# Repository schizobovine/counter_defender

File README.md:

counter_defender
================

PIR motion sensor alarm to keep the cats off the countertop. Modular. Also ridiculous.

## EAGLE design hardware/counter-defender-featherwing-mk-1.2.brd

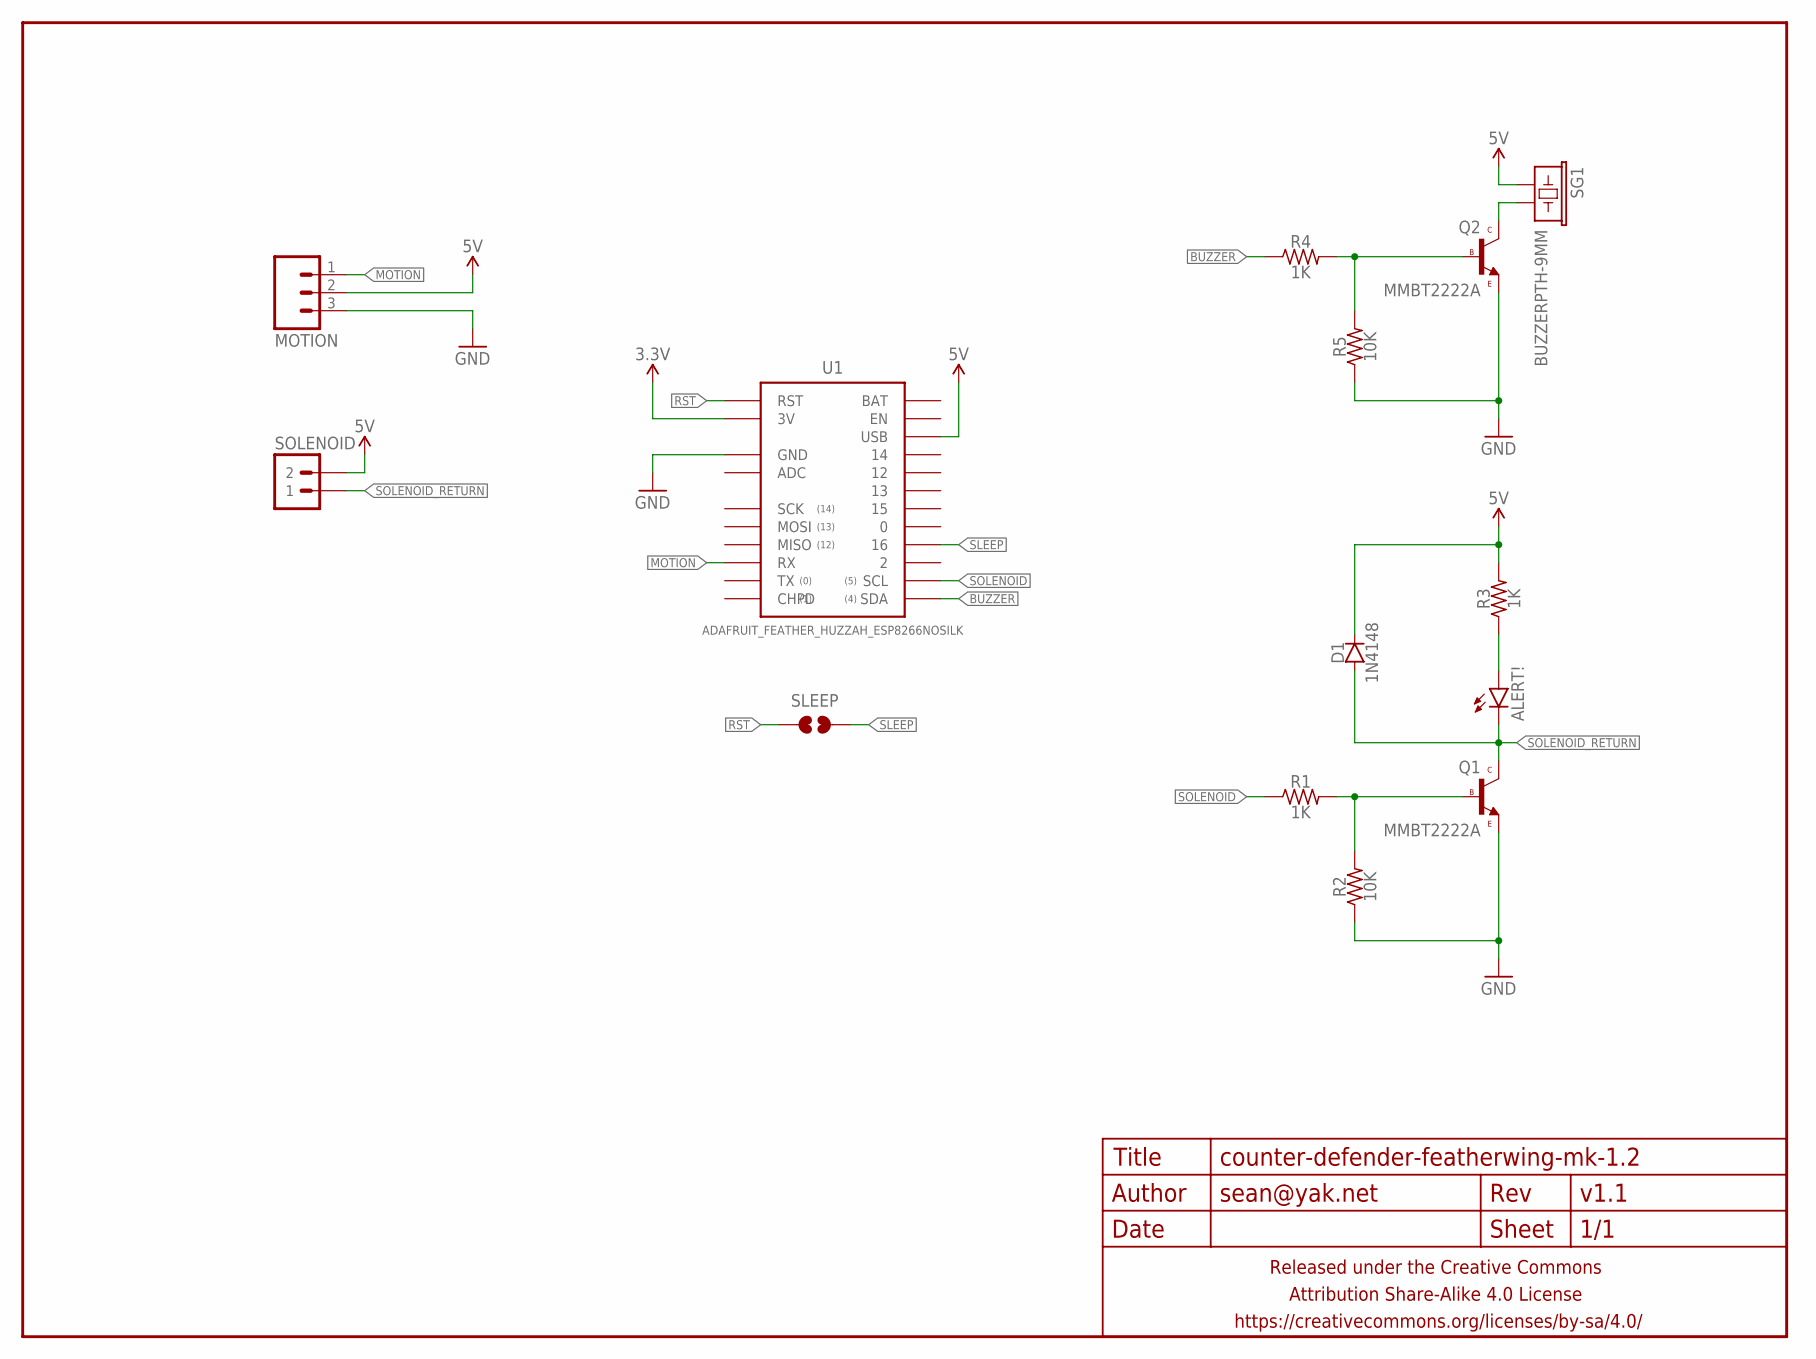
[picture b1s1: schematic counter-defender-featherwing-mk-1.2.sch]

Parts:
ALERT!: LED0603-TIGHT; LED-0603-TIGHT
D1: 1N4148; SOD123
FRAME1: FRAME-LETTERNO_PACKAGE; DUMMY
MOTION: M03PTH-CENTERED; 1X03-CENTERED
Q1, Q2: MMBT2222A; SOT23
R1, R3, R4: 1K; R0603-TIGHTER
R2, R5: 10K; R0603-TIGHTER
SG1: BUZZERPTH-9MM; BUZZER-PTH-9MM
SLEEP: JUMPER-PAD-2-NOYES_SILK; PAD-JUMPER-2-NO_YES_SILK
SOLENOID: M02PTH-CENTERED; 1X02-CENTER
U1: ADAFRUIT_FEATHER_HUZZAH_ESP8266NOSILK; ADAFRUIT_FEATHER_HUZZAH_NOSILK

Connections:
3.3V: U1.3V
5V: D1.C, MOTION.2, R3.2, SG1.+ (1), SOLENOID.2, U1.USB
BUZZER: R4.1, U1.SDA
GND: MOTION.3, Q1.2 (E), Q2.2 (E), R2.1, R5.1, U1.GND@0 (GND)
MOTION: MOTION.1, U1.RX
unnamed: ALERT!.A, R3.1
unnamed: Q1.1 (B), R1.2, R2.2
unnamed: Q2.3 (C), SG1.- (2)
unnamed: Q2.1 (B), R4.2, R5.2
RST: SLEEP.1, U1.RST
SLEEP: SLEEP.2, U1.16
SOLENOID: R1.1, U1.SCL
SOLENOID_RETURN: ALERT!.C, D1.A, Q1.3 (C), SOLENOID.1

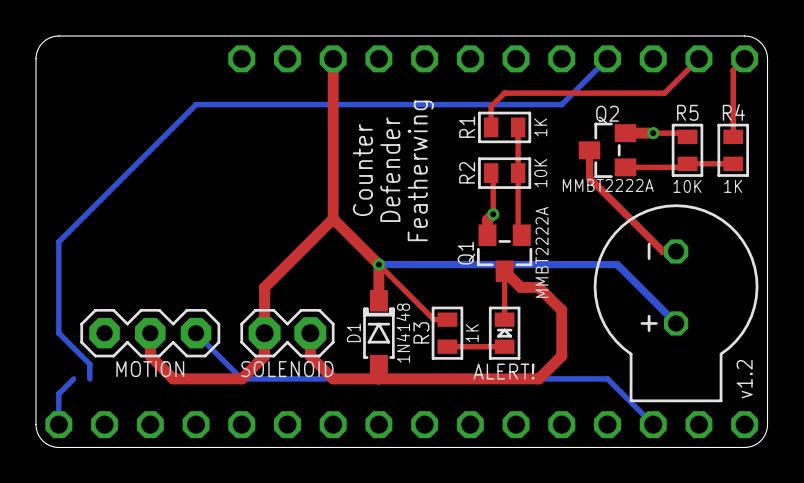
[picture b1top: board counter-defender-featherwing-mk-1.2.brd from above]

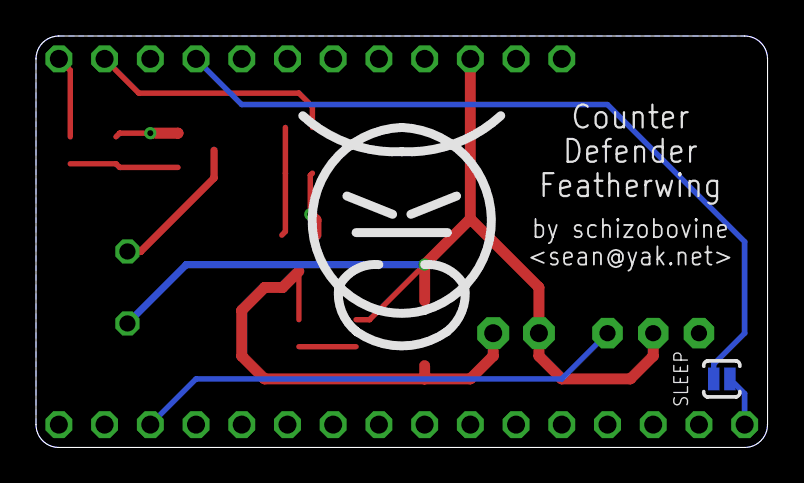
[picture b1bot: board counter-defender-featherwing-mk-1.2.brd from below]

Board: 2 copper layers, 40.6 x 22.9 mm, 16 parts (2 on the bottom side), 12 nets.

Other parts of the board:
U$1: COW

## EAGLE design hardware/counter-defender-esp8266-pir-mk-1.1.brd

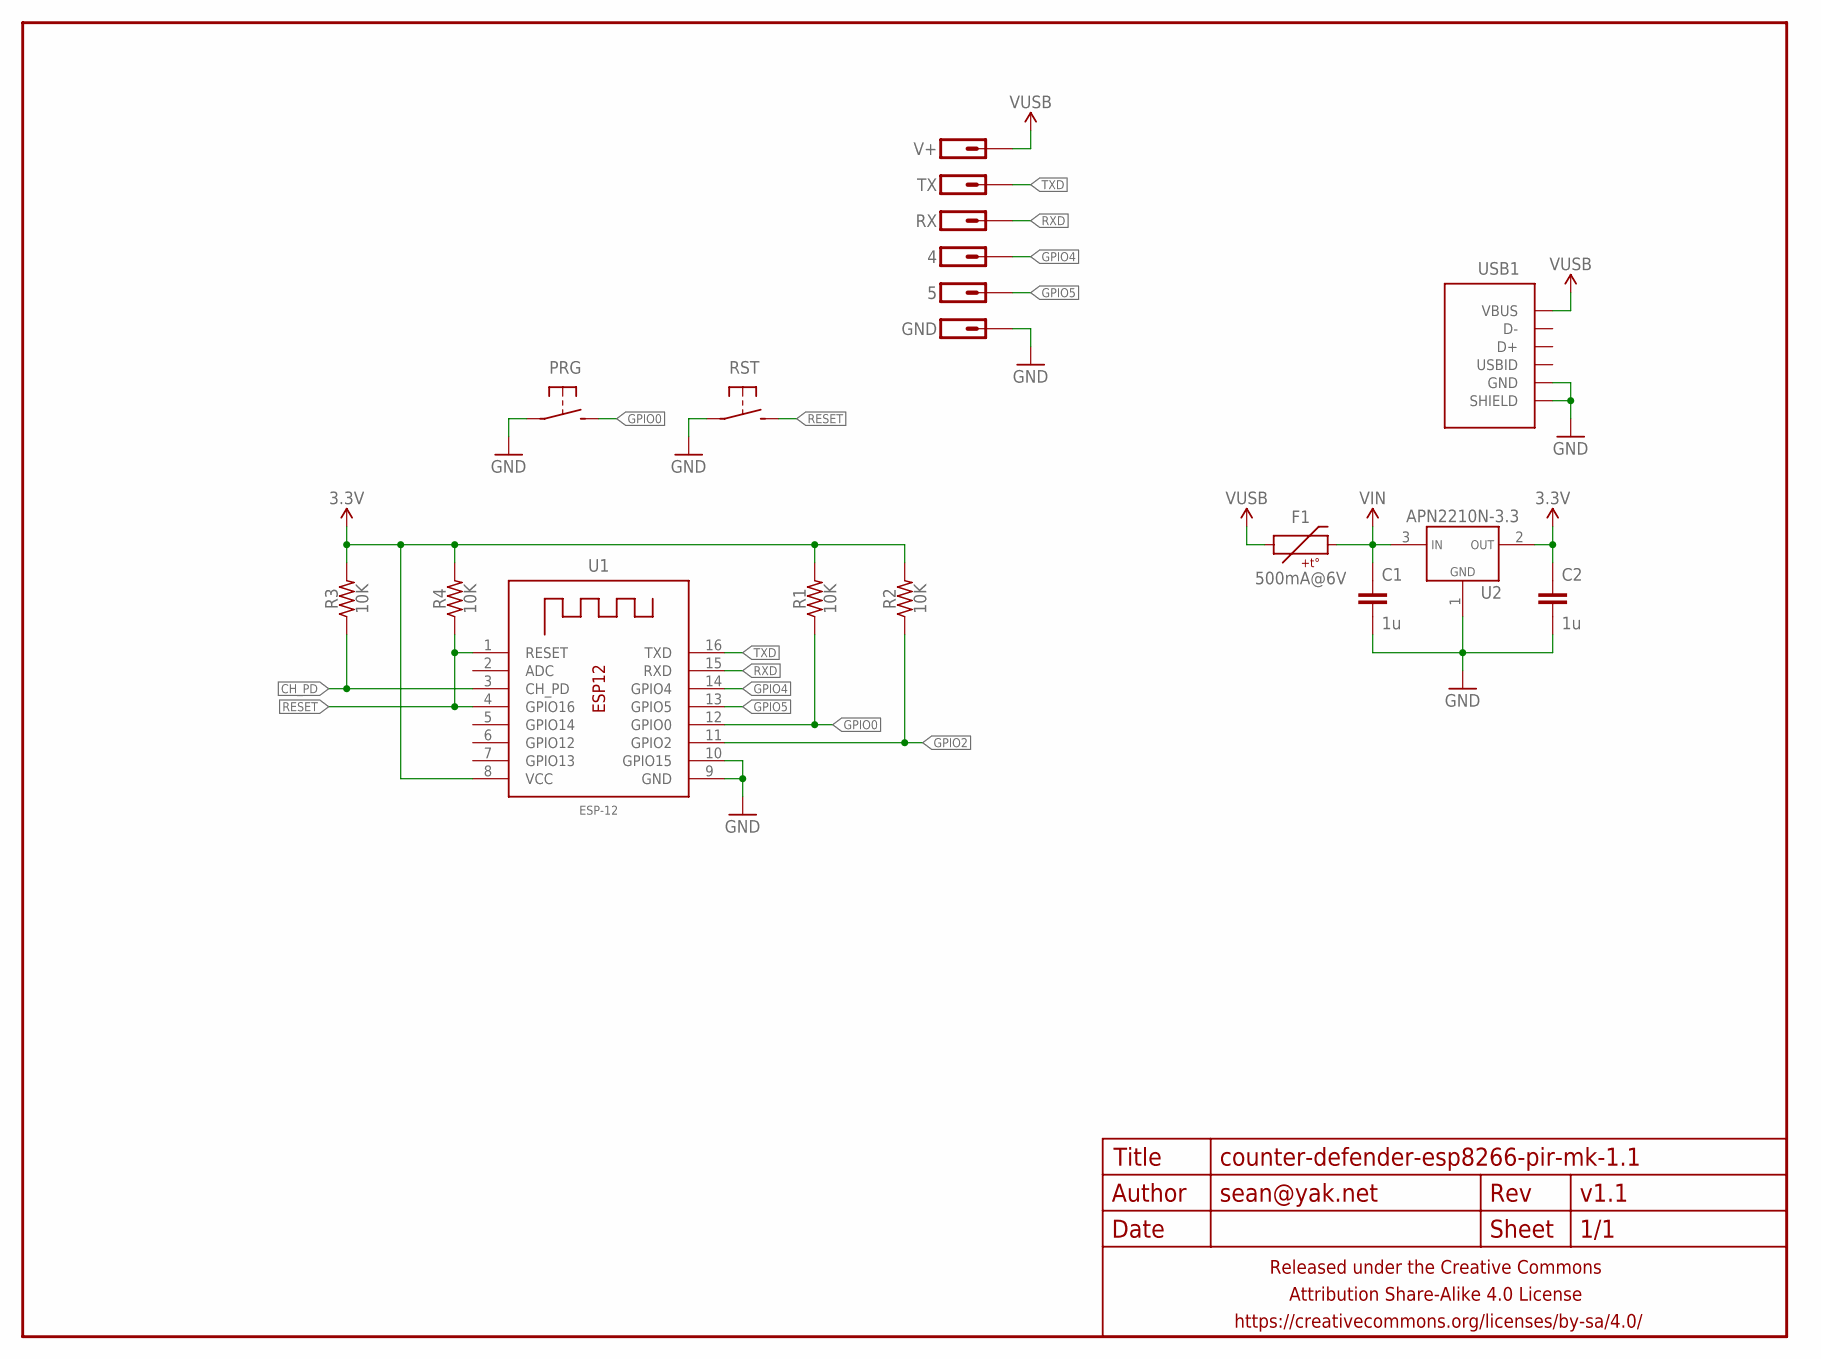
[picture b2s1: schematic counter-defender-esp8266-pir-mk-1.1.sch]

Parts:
4, 5: M01PTH; 1X01
C1, C2: 1u; C0603-TIGHTER
F1: 500mA@6V; 0603
FRAME1: FRAME-LETTERNO_PACKAGE; DUMMY
GND: M01PTH; 1X01
PRG: SPST-NO-TACTSMD-TINIER; TACTILE_SWITCH_SMD_TINY
R1, R2, R3, R4: 10K; R0603-TIGHTER
RST: SPST-NO-TACTSMD-TINIER; TACTILE_SWITCH_SMD_TINY
RX: M01PTH; 1X01
TX: M01PTH; 1X01
U1: ESP-12
U2: APN2210N-3.3; SOT23
USB1: USB-AB-SHIELDFCI-10103594-USB-MICRO-B-EVENLESSER; FCI-10103594-USB-MICRO-B-EVENLESSER
V+: M01PTH; 1X01

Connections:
3.3V: C2.1, R1.2, R2.2, R3.2, R4.2, U1.8 (VCC), U2.2 (VOUT)
CH_PD: R3.1, U1.3 (CH_PD)
GND: C1.2, C2.2, GND.1, PRG.P$1 (1), RST.P$1 (1), U1.9 (GND), U1.10 (GPIO15), U2.1 (GND), USB1.5 (GND), USB1.SHIELD@1 (SHIELD), USB1.SHIELD@2 (SHIELD), USB1.SHIELD@3 (SHIELD), USB1.SHIELD@4 (SHIELD), USB1.SHIELD@5 (SHIELD), USB1.SHIELD@6 (SHIELD)
GPIO0: PRG.P$2 (2), R1.1, U1.12 (GPIO0)
GPIO2: R2.1, U1.11 (GPIO2)
GPIO4: 4.1, U1.14 (GPIO4)
GPIO5: 5.1, U1.13 (GPIO5)
RESET: R4.1, RST.P$2 (2), U1.1 (RESET), U1.4 (GPIO16)
RXD: RX.1, U1.15 (RXD)
TXD: TX.1, U1.16 (TXD)
VIN: C1.1, F1.2, U2.3 (VIN)
VUSB: F1.1, USB1.1 (VBUS), V+.1

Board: 2 copper layers, 20 parts (1 on the bottom side), 12 nets, no tracks yet.

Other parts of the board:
U$2: COW_SMALL_NOTEXT

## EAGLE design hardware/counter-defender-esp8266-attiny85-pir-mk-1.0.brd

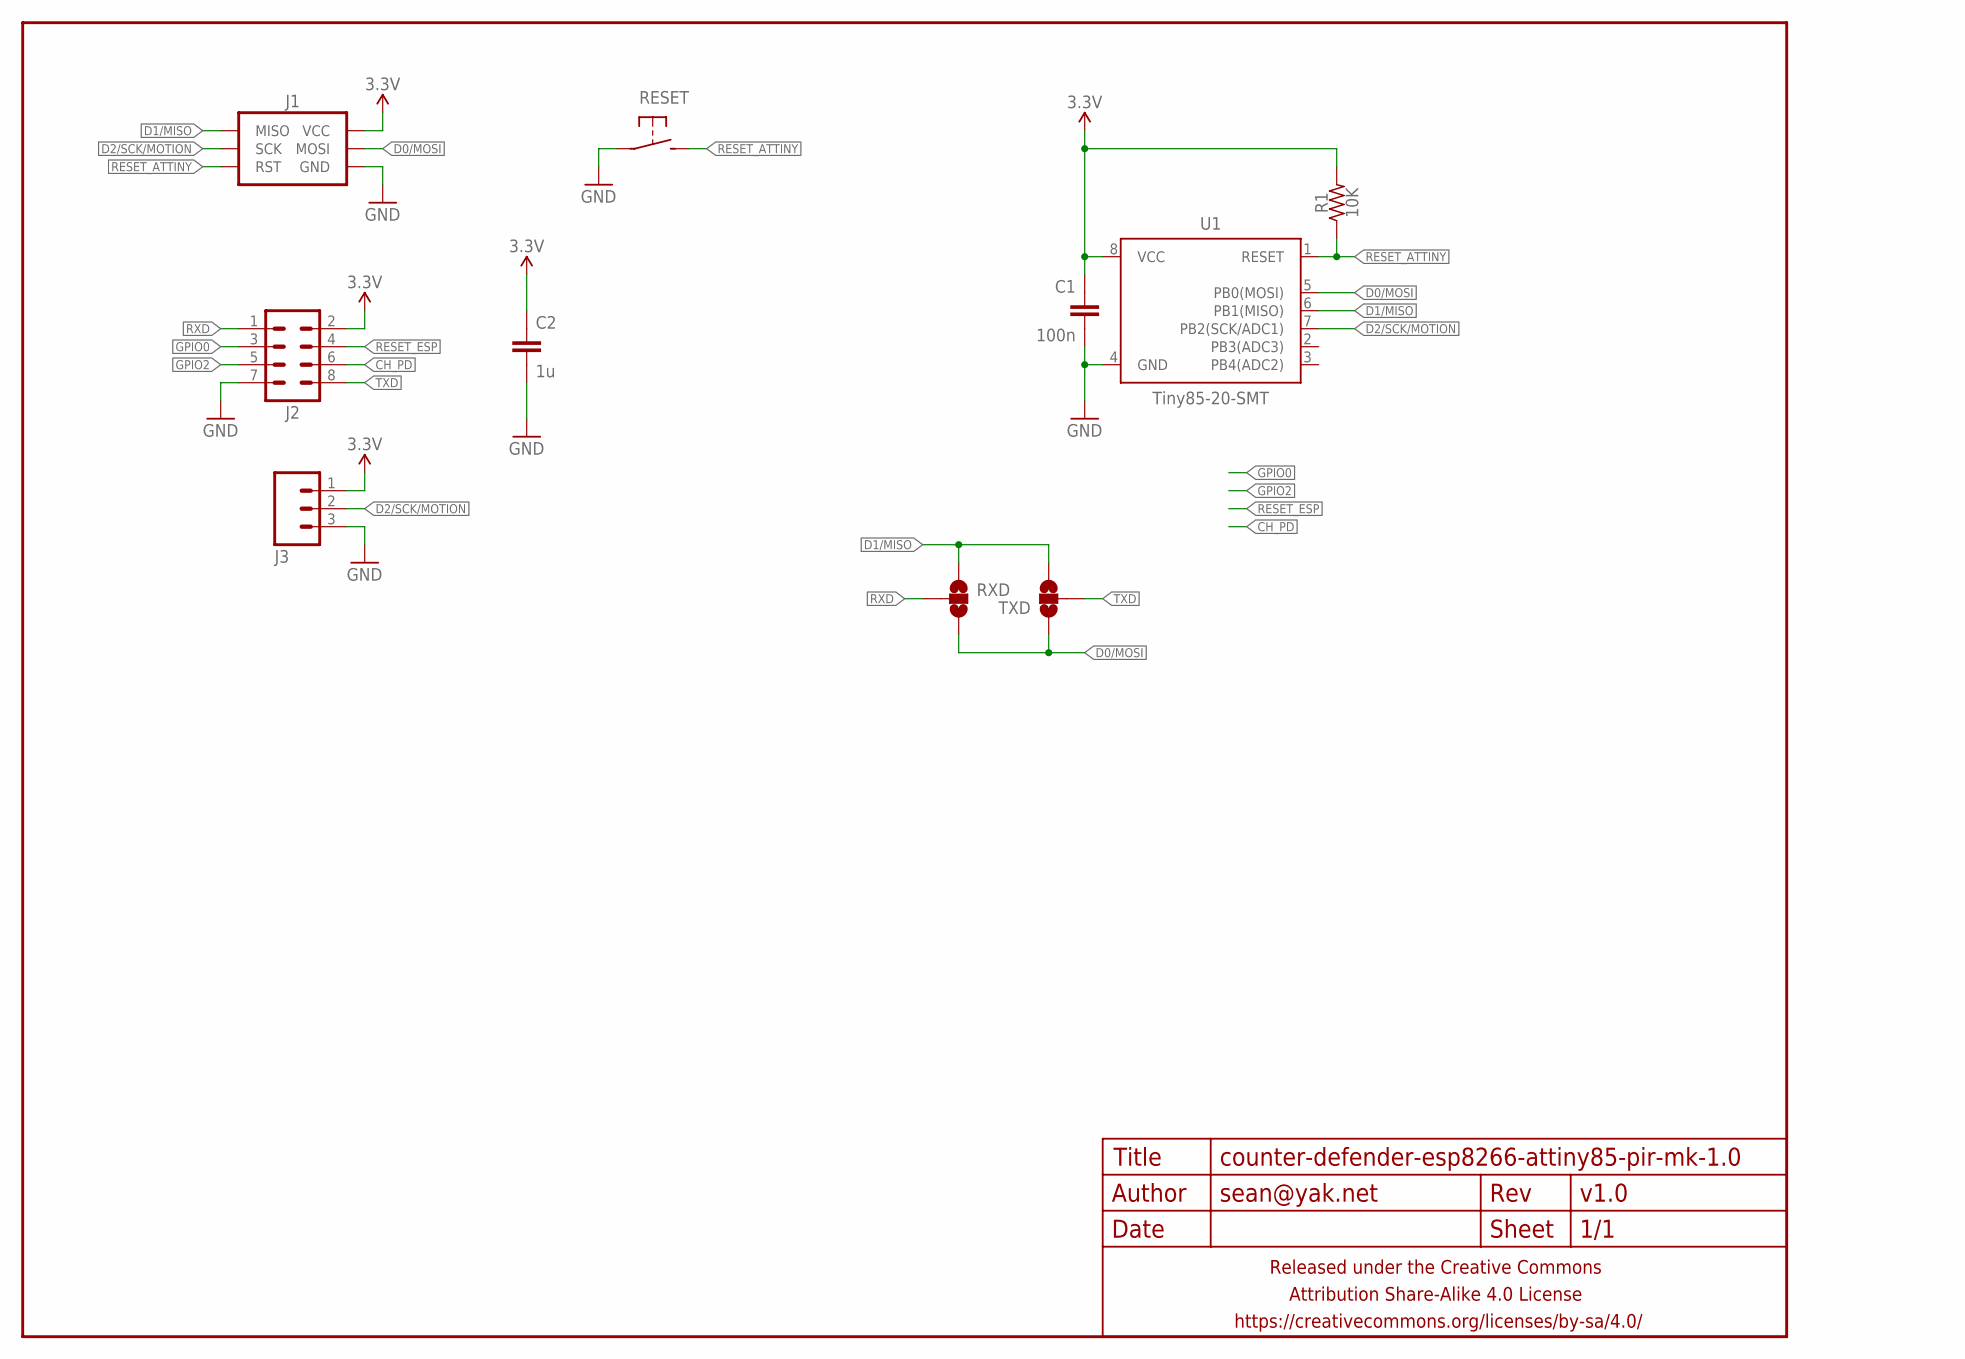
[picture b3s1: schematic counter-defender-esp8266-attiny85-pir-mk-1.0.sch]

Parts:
C1: 100n; C0603-TIGHTER
C2: 1u; C0603-TIGHTER
FRAME1: FRAME-LETTERNO_PACKAGE; DUMMY
J1: AVR_SPI_PRG_6PTH; 2X3
J2: M04X2PTH; 2X4_PTH
J3: M03PTH-CENTERED; 1X03-CENTERED
R1: 10K; R0603-TIGHTER
RESET: SPST-NO-TACTSMD-TINIER; TACTILE_SWITCH_SMD_TINY
RXD: JUMPER-PAD-3-NOSMALLER; PAD-JUMPER-3-NO_YES_SILK_FULL_BOX_SMALLER
TXD: JUMPER-PAD-3-NOSMALLER; PAD-JUMPER-3-NO_YES_SILK_FULL_BOX_SMALLER
U1: Tiny85-20-SMT; SO08-EIAJ

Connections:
3.3V: C1.1, C2.1, J1.2 (VCC), J2.2, J3.1, R1.2, U1.8 (VCC)
CH_PD: J2.6
D0/MOSI: J1.4 (MOSI), RXD.3, TXD.1, U1.5 (PB0(MOSI))
D1/MISO: J1.1 (MISO), RXD.1, TXD.3, U1.6 (PB1(MISO))
D2/SCK/MOTION: J1.3 (SCK), J3.2, U1.7 (PB2(SCK/ADC1))
GND: C1.2, C2.2, J1.6 (GND), J2.7, J3.3, RESET.P$1 (1), U1.4 (GND)
GPIO0: J2.3
GPIO2: J2.5
RESET_ATTINY: J1.5 (RST), R1.1, RESET.P$2 (2), U1.1 (RESET)
RESET_ESP: J2.4
RXD: J2.1
TXD: J2.8, TXD.2

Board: 2 copper layers, 12 parts (1 on the bottom side), 7 nets, no tracks yet.

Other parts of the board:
U$1: COW

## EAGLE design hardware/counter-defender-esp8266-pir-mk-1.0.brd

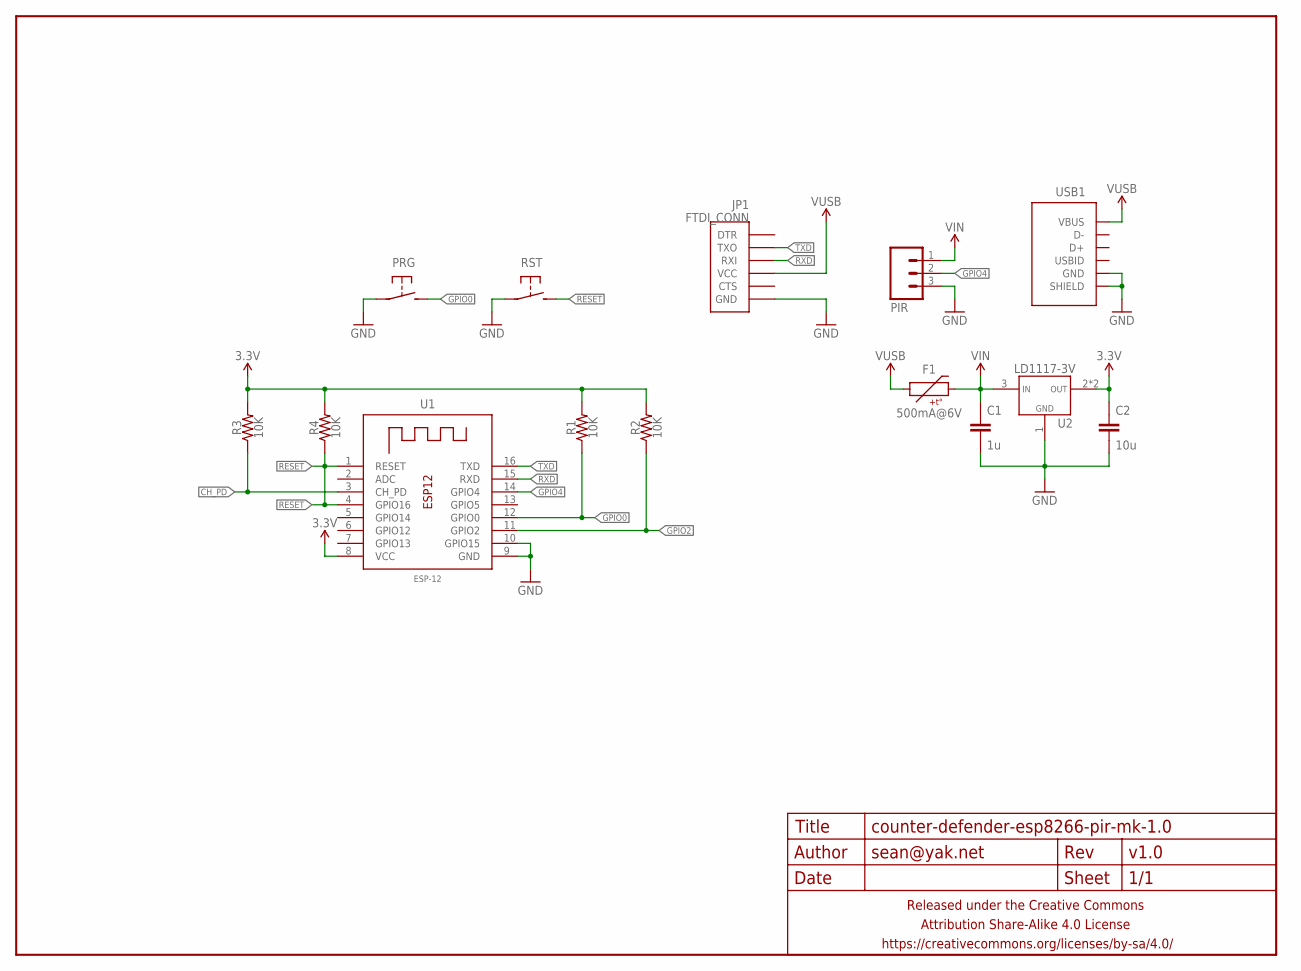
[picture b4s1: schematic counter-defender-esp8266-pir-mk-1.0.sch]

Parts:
C1: 1u; C0805-TIGHTER
C2: 10u; C0805-TIGHTER
F1: 500mA@6V; PTC0805
FRAME1: FRAME-LETTERNO_PACKAGE; DUMMY
JP1: FTDI_CONN
PIR: M03PTH-CENTERED; 1X03-CENTERED
PRG: SPST-NO-TACTSMD-TINIER; TACTILE_SWITCH_SMD_TINY
R1, R2, R3, R4: 10K; R0603-TIGHTER
RST: SPST-NO-TACTSMD-TINIER; TACTILE_SWITCH_SMD_TINY
U1: ESP-12
U2: LD1117-3V; SOT223
USB1: USB-AB-SHIELDFCI-10103594-USB-MICRO-B-EVENLESS; FCI-10103594-USB-MICRO-B-EVENLESS

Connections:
3.3V: C2.1, R1.2, R2.2, R3.2, R4.2, U1.8 (VCC), U2.2 (VOUT), U2.4 (VOUT)
CH_PD: R3.1, U1.3 (CH_PD)
GND: C1.2, C2.2, JP1.GND, PIR.3, PRG.P$1 (1), RST.P$1 (1), U1.9 (GND), U1.10 (GPIO15), U2.1 (GND), USB1.5 (GND), USB1.SHIELD@1 (SHIELD), USB1.SHIELD@2 (SHIELD), USB1.SHIELD@3 (SHIELD), USB1.SHIELD@4 (SHIELD), USB1.SHIELD@5 (SHIELD), USB1.SHIELD@6 (SHIELD)
GPIO0: PRG.P$2 (2), R1.1, U1.12 (GPIO0)
GPIO2: R2.1, U1.11 (GPIO2)
GPIO4: PIR.2, U1.14 (GPIO4)
RESET: R4.1, RST.P$2 (2), U1.1 (RESET), U1.4 (GPIO16)
RXD: JP1.RXI, U1.15 (RXD)
TXD: JP1.TXO, U1.16 (TXD)
VIN: C1.1, F1.2, PIR.1, U2.3 (VIN)
VUSB: F1.1, JP1.VCC, USB1.1 (VBUS)

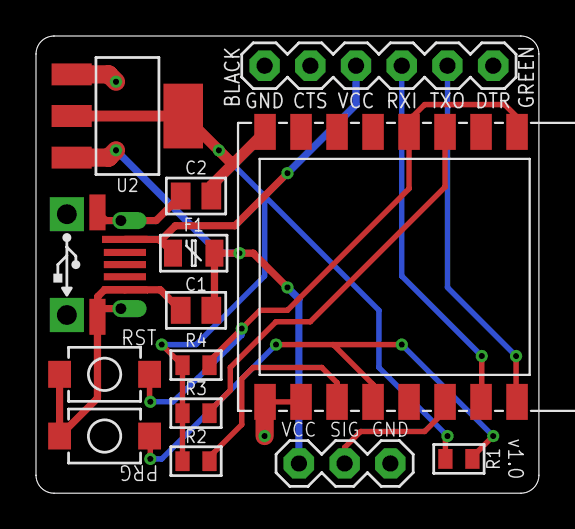
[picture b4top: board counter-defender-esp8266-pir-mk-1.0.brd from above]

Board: 2 copper layers, 27.9 x 25.4 mm, 16 parts (1 on the bottom side), 11 nets.

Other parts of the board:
U$2: COW_SMALL_NOTEXT

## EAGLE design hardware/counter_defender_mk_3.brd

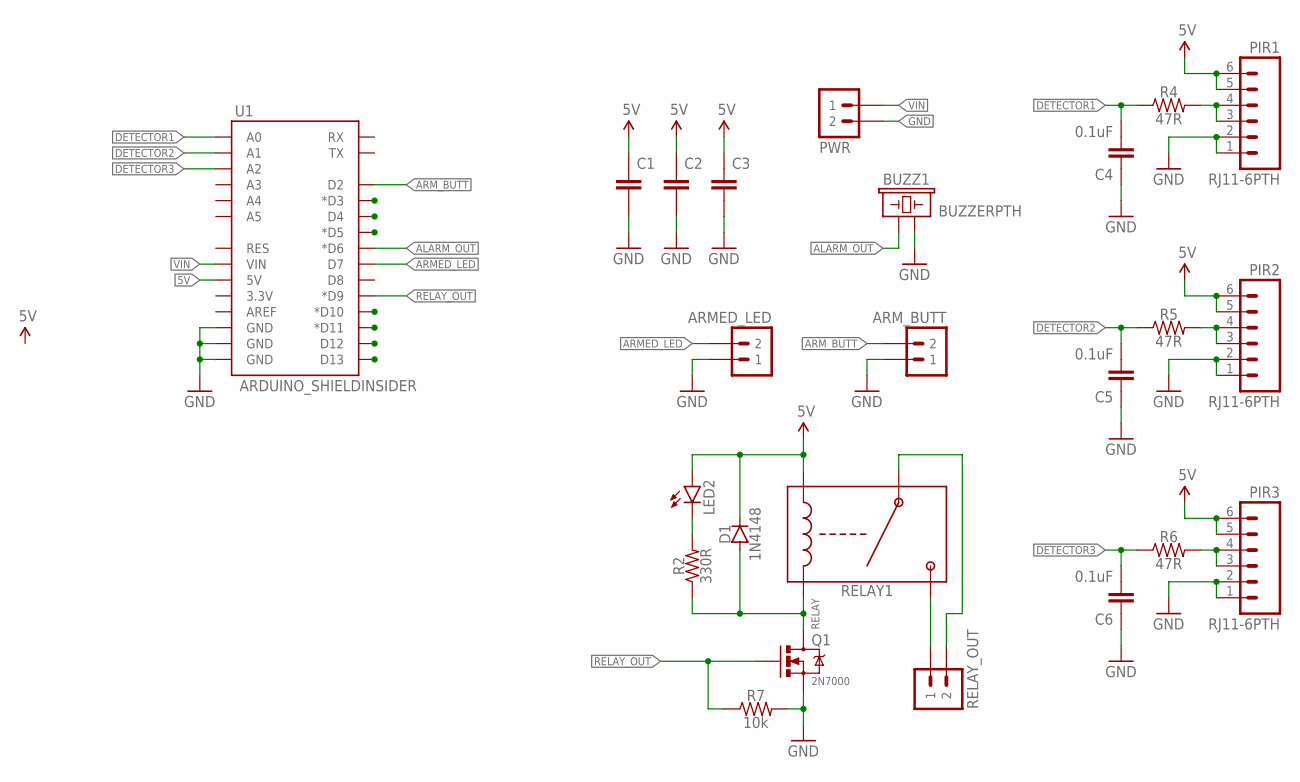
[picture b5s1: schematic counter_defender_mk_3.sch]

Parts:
ARMED_LED: M02JST-PTH-VERT; JST-2-PH-VERT-PTH
ARM_BUTT: M02JST-PTH-VERT; JST-2-PH-VERT-PTH
BUZZ1: BUZZERPTH; BUZZER-12MM
C1, C2, C3: CAPACITOR-CERAMIC025-024X044; C025-024X044
C4, C5, C6: 0.1uF; C025-024X044
D1: 1N4148; DIODE-7.62MM
LED2: LED3MM
PIR1, PIR2, PIR3: RJ11-6PTH; RJ11-6
PWR: M02JST-PTH-VERT; JST-2-PH-VERT-PTH
Q1: 2N7000; TO-92-AMMO
R2: 330R; RESISTOR-AXIAL-PTH-7.62MM
R4, R5, R6: 47R; RESISTOR-AXIAL-PTH-6.35MM
R7: 10k; RESISTOR-AXIAL-PTH-7.62MM
RELAY1: RELAY-SPST-NOT77; T77-SPST-NO-RELAY
RELAY_OUT: M02SCREWTERM_2.54MM; 1X02_2.54_SCREWTERM
U1: ARDUINO_SHIELDINSIDER; ARDUINO_SHIELD_NOOUTLINE_INSIDE

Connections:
5V: C1.1, C2.1, C3.1, D1.K (C), LED2.A, PIR1.5, PIR1.6, PIR2.5, PIR2.6, PIR3.5, PIR3.6, RELAY1.COIL2, U1.5V
ALARM_OUT: BUZZ1.+ (1), U1.D6 (*D6)
ARMED_LED: ARMED_LED.2, U1.D7
ARM_BUTT: ARM_BUTT.2, U1.D2
DETECTOR1: C4.2, R4.P$1 (1), U1.A0
DETECTOR2: C5.2, R5.P$1 (1), U1.A1
DETECTOR3: C6.2, R6.P$1 (1), U1.A2
GND: ARMED_LED.1, ARM_BUTT.1, BUZZ1.- (2), C1.2, C2.2, C3.2, C4.1, C5.1, C6.1, PIR1.1, PIR1.2, PIR2.1, PIR2.2, PIR3.1, PIR3.2, PWR.2, Q1.1 (S), R7.P$2 (2), U1.GND@0 (GND), U1.GND@1 (GND), U1.GND@2 (GND)
unnamed: PIR1.3, PIR1.4, R4.P$2 (2)
unnamed: PIR2.3, PIR2.4, R5.P$2 (2)
unnamed: PIR3.3, PIR3.4, R6.P$2 (2)
unnamed: LED2.K (C), R2.P$2 (2)
unnamed: RELAY1.NO, RELAY_OUT.P1 (1)
unnamed: RELAY1.COM, RELAY_OUT.P2 (2)
RELAY: D1.A, Q1.3 (D), R2.P$1 (1), RELAY1.COIL1
RELAY_OUT: Q1.2 (G), R7.P$1 (1), U1.D9 (*D9)
VIN: PWR.1, U1.VIN

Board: 2 copper layers, 24 parts (0 on the bottom side), 17 nets, no tracks yet.

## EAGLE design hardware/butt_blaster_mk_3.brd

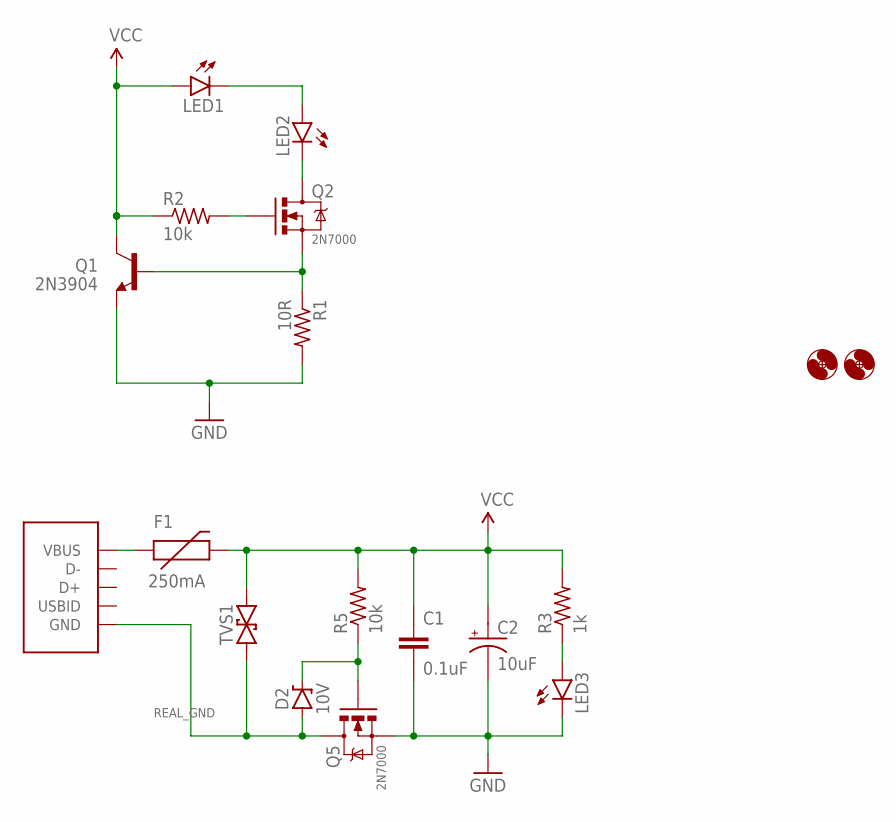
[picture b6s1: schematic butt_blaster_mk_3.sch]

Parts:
C1: 0.1uF; C025-024X044
C2: 10uF; E2,5-6
D2: 10V; DIODE-7.68MM
F1: 250mA; PTC
H1, H2: HOLE#2; HOLE-#2
LED1, LED2: LED5MM_SHORTPADS
LED3: LED3MM
PWR: USB-ABCOMBO; USB-MICRO-B-FCI-CUTOUT
Q1: 2N3904; TO-92-AMMO
Q2, Q5: 2N7000; TO-92-AMMO
R1: 10R; RESISTOR-AXIAL-PTH-10.16MM
R2: 10k; RESISTOR-AXIAL-PTH-6.35MM
R3: 1k; RESISTOR-AXIAL-PTH-6.35MM
R5: 10k; RESISTOR-AXIAL-PTH-7.68MM
TVS1: TVSDO-41-TVS-BIDIRECTIONAL; DO-41-TVS

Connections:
GND: C1.2, C2.-, LED3.K (C), Q1.1 (E), Q5.1 (S), R1.P$2 (2)
unnamed: LED1.K (C), LED2.A
unnamed: LED3.A, R3.P$1 (1)
unnamed: LED2.K (C), Q2.3 (D)
unnamed: F1.P$1 (1), PWR.1 (VBUS)
unnamed: D2.K (C), Q5.2 (G), R5.P$1 (1)
unnamed: Q1.2 (B), Q2.1 (S), R1.P$1 (1)
unnamed: Q2.2 (G), R2.P$2 (2)
REAL_GND: D2.A, PWR.5 (GND), PWR.P$1 (GND), PWR.P$2 (GND), Q5.3 (D), TVS1.P$1 (1)
VCC: C1.1, C2.+, F1.P$2 (2), LED1.A, Q1.3 (C), R2.P$1 (1), R3.P$2 (2), R5.P$2 (2), TVS1.P$2 (2)

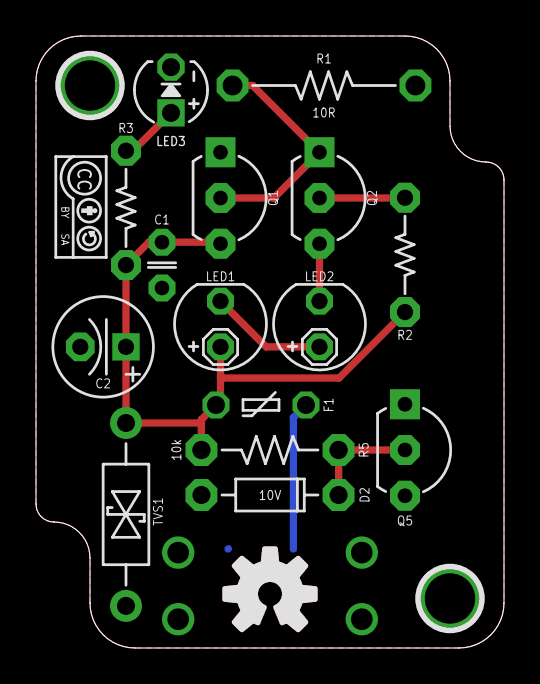
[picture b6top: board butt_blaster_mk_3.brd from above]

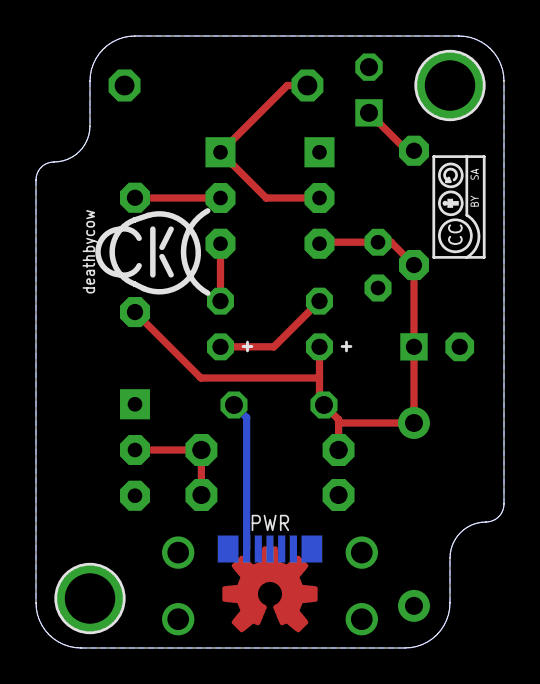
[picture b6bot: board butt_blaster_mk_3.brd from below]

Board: 2 copper layers, 26.0 x 34.0 mm, 22 parts (3 on the bottom side), 10 nets.

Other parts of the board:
U$2: COW_SMALL
U$3, U$4: CC-BY-SA-4.0-NO-URL
U$5: OSHWLOGO_TOP_0.2_A

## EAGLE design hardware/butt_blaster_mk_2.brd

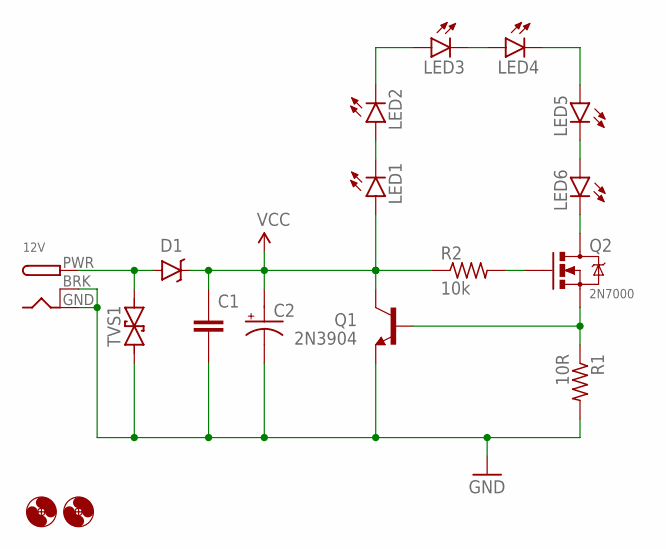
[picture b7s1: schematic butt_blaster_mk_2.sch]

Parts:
12V: DCBARRELPTH; DCJACK_2MM_PTH
C1: CAPACITOR-CERAMIC025-024X044; C025-024X044
C2: CAPACITOR-POLARIZEDE2.5-6; E2,5-6
D1: DIODE-SCHOTTKYPTH-8.38MM; DIODE-8.38MM
H1, H2: HOLE#2; HOLE-#2
LED1, LED2, LED3, LED4, LED5, LED6: LED5MM_SHORTPADS
Q1: 2N3904; TO-92-AMMO
Q2: 2N7000; TO-92-AMMO
R1: 10R; RESISTOR-AXIAL-PTH-7.68MM
R2: 10k; RESISTOR-AXIAL-PTH-7.68MM
TVS1: TVSDO-41-TVS-BIDIRECTIONAL; DO-41-TVS

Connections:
GND: 12V.BRK, 12V.GND, C1.2, C2.-, Q1.1 (E), R1.P$2 (2), TVS1.P$1 (1)
unnamed: LED3.K (C), LED4.A
unnamed: LED2.K (C), LED3.A
unnamed: LED4.K (C), LED5.A
unnamed: LED1.K (C), LED2.A
unnamed: Q1.2 (B), Q2.1 (S), R1.P$1 (1)
unnamed: LED6.K (C), Q2.3 (D)
unnamed: Q2.2 (G), R2.P$2 (2)
unnamed: LED5.K (C), LED6.A
unnamed: 12V.PWR, D1.A, TVS1.P$2 (2)
VCC: C1.1, C2.+, D1.K (C), LED1.A, Q1.3 (C), R2.P$1 (1)

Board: 2 copper layers, 17 parts (0 on the bottom side), 11 nets, no tracks yet.

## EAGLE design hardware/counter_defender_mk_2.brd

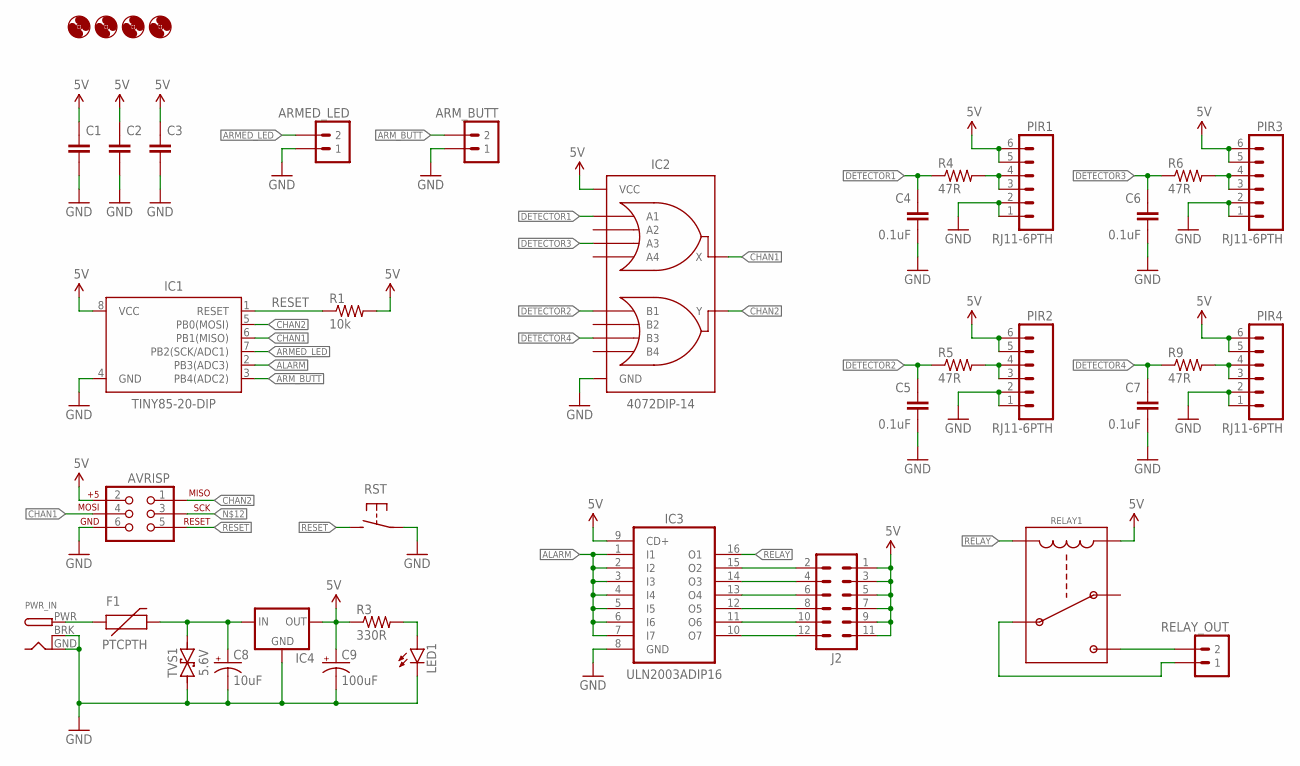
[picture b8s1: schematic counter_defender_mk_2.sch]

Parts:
ARMED_LED: M02JST-PTH-VERT; JST-2-PH-VERT-PTH
ARM_BUTT: M02JST-PTH-VERT; JST-2-PH-VERT-PTH
AVRISP: AVR_SPI_PRG_6PTH; 2X3
C1, C2, C3: CAPACITOR-CERAMIC025-024X044; C025-024X044
C4, C5, C6, C7: 0.1uF; C025-024X044
C8: 10uF; E2-5
C9: 100uF; E2,5-6
F1: PTCPTH; PTC
H1, H2, H3, H4: HOLE#2; HOLE-#2
IC1: TINY85-20-DIP; DIP08
IC2: 4072DIP-14; DIL14
IC3: ULN2003ADIP16; DIL16
IC4: L7805; TO220V
J2: M06X2PTH; 2X6_PTH
LED1: LED3MM
PIR1, PIR2, PIR3, PIR4: RJ11-6PTH; RJ11-6
PWR_IN: DCBARRELPTH; DCJACK_2MM_PTH
R1: 10k; RESISTOR-AXIAL-PTH-6.35MM
R3: 330R; RESISTOR-AXIAL-PTH-6.35MM
R4, R5, R6, R9: 47R; RESISTOR-AXIAL-PTH-6.35MM
RELAY1: RELAY-SPDTMC25120; RELAY-SPDT-MC25120
RELAY_OUT: M02SCREWTERM_2.54MM; 1X02_2.54_SCREWTERM
RST: SPST-NO-TACT6MM-PTH; DTS-6
TVS1: 5.6V; DO-41-TVS

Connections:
5V: AVRISP.2, C1.1, C2.1, C3.1, C9.+, IC1.8 (VCC), IC2.14 (VCC), IC3.9 (CD+), IC4.3 (OUT), J2.1, J2.3, J2.5, J2.7, J2.9, J2.11, PIR1.5, PIR1.6, PIR2.5, PIR2.6, PIR3.5, PIR3.6, PIR4.5, PIR4.6, R1.P$2 (2), R3.P$1 (1), RELAY1.CNTL2
ALARM: IC1.2 (PB3(ADC3)), IC3.1 (I1), IC3.2 (I2), IC3.3 (I3), IC3.4 (I4), IC3.5 (I5), IC3.6 (I6), IC3.7 (I7)
ARMED_LED: ARMED_LED.2, IC1.7 (PB2(SCK/ADC1))
ARM_BUTT: ARM_BUTT.2, IC1.3 (PB4(ADC2))
CHAN1: AVRISP.4, IC1.6 (PB1(MISO)), IC2.1 (X)
CHAN2: AVRISP.1, IC1.5 (PB0(MOSI)), IC2.13 (Y)
DETECTOR1: C4.1, IC2.2 (A1), R4.P$1 (1)
DETECTOR2: C5.1, IC2.9 (B1), R5.P$1 (1)
DETECTOR3: C6.1, IC2.4 (A3), R6.P$1 (1)
DETECTOR4: C7.1, IC2.11 (B3), R9.P$1 (1)
GND: ARMED_LED.1, ARM_BUTT.1, AVRISP.6, C1.2, C2.2, C3.2, C4.2, C5.2, C6.2, C7.2, C8.-, C9.-, IC1.4 (GND), IC2.7 (GND), IC3.8 (GND), IC4.2 (GND), LED1.K (C), PIR1.1, PIR1.2, PIR2.1, PIR2.2, PIR3.1, PIR3.2, PIR4.1, PIR4.2, PWR_IN.BRK, PWR_IN.GND, RST.1, RST.2 (1), TVS1.P$1 (1)
unnamed: C8.+, F1.P$2 (2), IC4.1 (IN), TVS1.P$2 (2)
unnamed: PIR1.3, PIR1.4, R4.P$2 (2)
unnamed: PIR2.3, PIR2.4, R5.P$2 (2)
unnamed: PIR3.3, PIR3.4, R6.P$2 (2)
unnamed: PIR4.3, PIR4.4, R9.P$2 (2)
unnamed: LED1.A, R3.P$2 (2)
unnamed: F1.P$1 (1), PWR_IN.PWR
unnamed: IC3.15 (O2), J2.2
unnamed: IC3.14 (O3), J2.4
unnamed: IC3.13 (O4), J2.6
unnamed: IC3.12 (O5), J2.8
unnamed: IC3.11 (O6), J2.10
unnamed: IC3.10 (O7), J2.12
unnamed: RELAY1.COM, RELAY1.COM2 (COM), RELAY_OUT.P1 (1)
unnamed: RELAY1.NO, RELAY_OUT.P2 (2)
RELAY: IC3.16 (O1), RELAY1.CNTL1
RESET: AVRISP.5, IC1.1 (RESET), R1.P$1 (1), RST.3 (2), RST.4 (2)

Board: 2 copper layers, 38 parts (0 on the bottom side), 28 nets, no tracks yet.

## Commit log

2014-12-11 revion 1 of mark 2
2014-12-17 board destined to be an IR blaster (nominally to catch my cat's butts on the counter, hence the name)
2014-12-18 more butts
2014-12-18 basing this on a AC/DC LED driver
2014-12-18 renaming and creating new version with a simpler LED drive circuit to cheat and use a wall-wort adapter.
2014-12-19 butts
2014-12-19 more butts, only twooooo leds this time
2014-12-19 shuffled up componets but still not happy
2015-01-23 derp
2017-04-09 featherwing for adafruit huzzah feather
2017-04-09 rearrange for multiple version of the firmware
2017-04-18 new connector board
2017-04-22 more boards
2017-08-27 blah
2017-08-28 basic wireless configurator
2017-08-28 turns out esp8266 gpio pin 2 is not a good choice for the buzzer

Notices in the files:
parts and their libraries:
a_parts: Released under the Creative Commons Attribution Share-Alike 4.0 License
a_parts: https://creativecommons.org/licenses/by-sa/4.0
a_parts: Released under the Creative Commons
